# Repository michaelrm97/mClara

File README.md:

# Clara Mini

## Background

The other Project C.L.A.R.A (Christmas Light Array Running on Azure) was conceived in 2020 as an LED Christmas light display controllable from the web. See [https://github.com/michaelrm97/clara](https://github.com/michaelrm97/clara) for information about the previous project.

## Components

There are three components of this:

- PCB with an LED light array in the shape of a Christmas card
- Laser cut plywood covers glued to the back and front of the PCB. The front contains a Christmas tree graphic and the back contains a festive greeting with a QR code linking to a personal message
- Web app hosting the card message. See [README](./software/README.md)

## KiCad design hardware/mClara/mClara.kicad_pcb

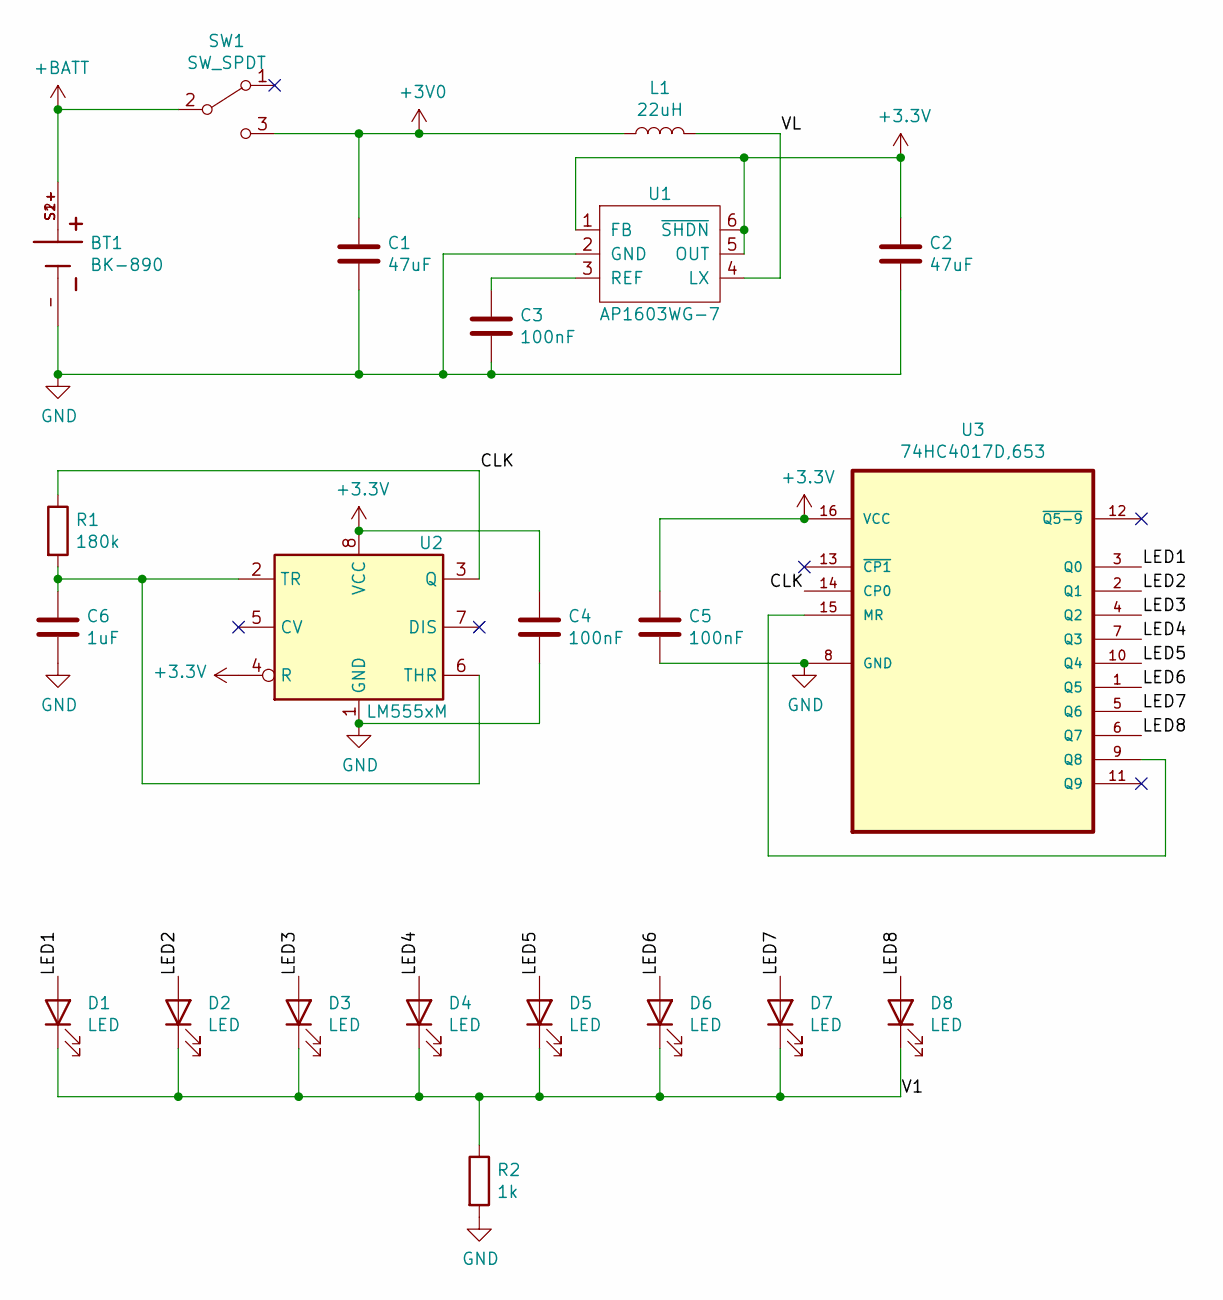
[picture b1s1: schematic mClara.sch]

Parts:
BT1: BK-890; BAT_BK-890; PARTREV E
C1, C2: 47uF; C_1206_3216Metric_Pad1.33x1.80mm_HandSolder; MPN CL31A476MQHNNWE
C3, C4, C5: 100nF; C_0603_1608Metric_Pad1.08x0.95mm_HandSolder; MPN CL10B104KB8NNWC
C6: 1uF; C_0603_1608Metric_Pad1.08x0.95mm_HandSolder; MPN CL10A105KO8NNNC
D1, D2, D3, D4, D5, D6, D7, D8: LED; LED_0603_1608Metric_Pad1.05x0.95mm_HandSolder; MPN IN-S63AT5UW
L1: 22uH; L_1812_4532Metric_Pad1.30x3.40mm_HandSolder; MPN LQH43PN220M26L
R1: 180k; R_0603_1608Metric_Pad0.98x0.95mm_HandSolder; MPN RMCF0603FT180K
R2: 1k; R_0603_1608Metric_Pad0.98x0.95mm_HandSolder; MPN RMCF0603JJ1K00
SW1: SW_SPDT; SW_PCM12SMTR; MPN PCM12SMTR
U1: AP1603WG-7; SOT-23-6_Handsoldering; MPN AP1603WG-7
U2: LM555xM; SOIC-8_3.9x4.9mm_P1.27mm; MPN TLC555IDR
U3: 74HC4017D,653; SO-16_3.9x9.9mm_P1.27mm; MPN 74HC4017D,653

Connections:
+3V0: C1.1, L1.1, SW1.3 (C)
+3V3: C2.1, C4.1, C5.1, U1.1 (FB), U1.5 (OUT), U1.6 (~SHDN), U2.4 (R), U2.8 (VCC), U3.16 (VCC)
+BATT: BT1.S1+, BT1.S2+, SW1.2 (B)
/CLK: R1.1, U2.3 (Q), U3.14 (CP0)
/LED1: D1.2 (A), U3.3 (Q0)
/LED2: D2.2 (A), U3.2 (Q1)
/LED3: D3.2 (A), U3.4 (Q2)
/LED4: D4.2 (A), U3.7 (Q3)
/LED5: D5.2 (A), U3.10 (Q4)
/LED6: D6.2 (A), U3.1 (Q5)
/LED7: D7.2 (A), U3.5 (Q6)
/LED8: D8.2 (A), U3.6 (Q7)
/V1: D1.1 (K), D2.1 (K), D3.1 (K), D4.1 (K), D5.1 (K), D6.1 (K), D7.1 (K), D8.1 (K), R2.1
/VL: L1.2, U1.4 (LX)
GND: BT1.-, C1.2, C2.2, C3.2, C4.2, C5.2, C6.2, R2.2, U1.2 (GND), U2.1 (GND), U3.8 (GND)
unnamed: C3.1, U1.3 (REF)
unnamed: C6.1, R1.2, U2.2 (TR), U2.6 (THR)
unnamed: U3.9 (Q8), U3.15 (MR)

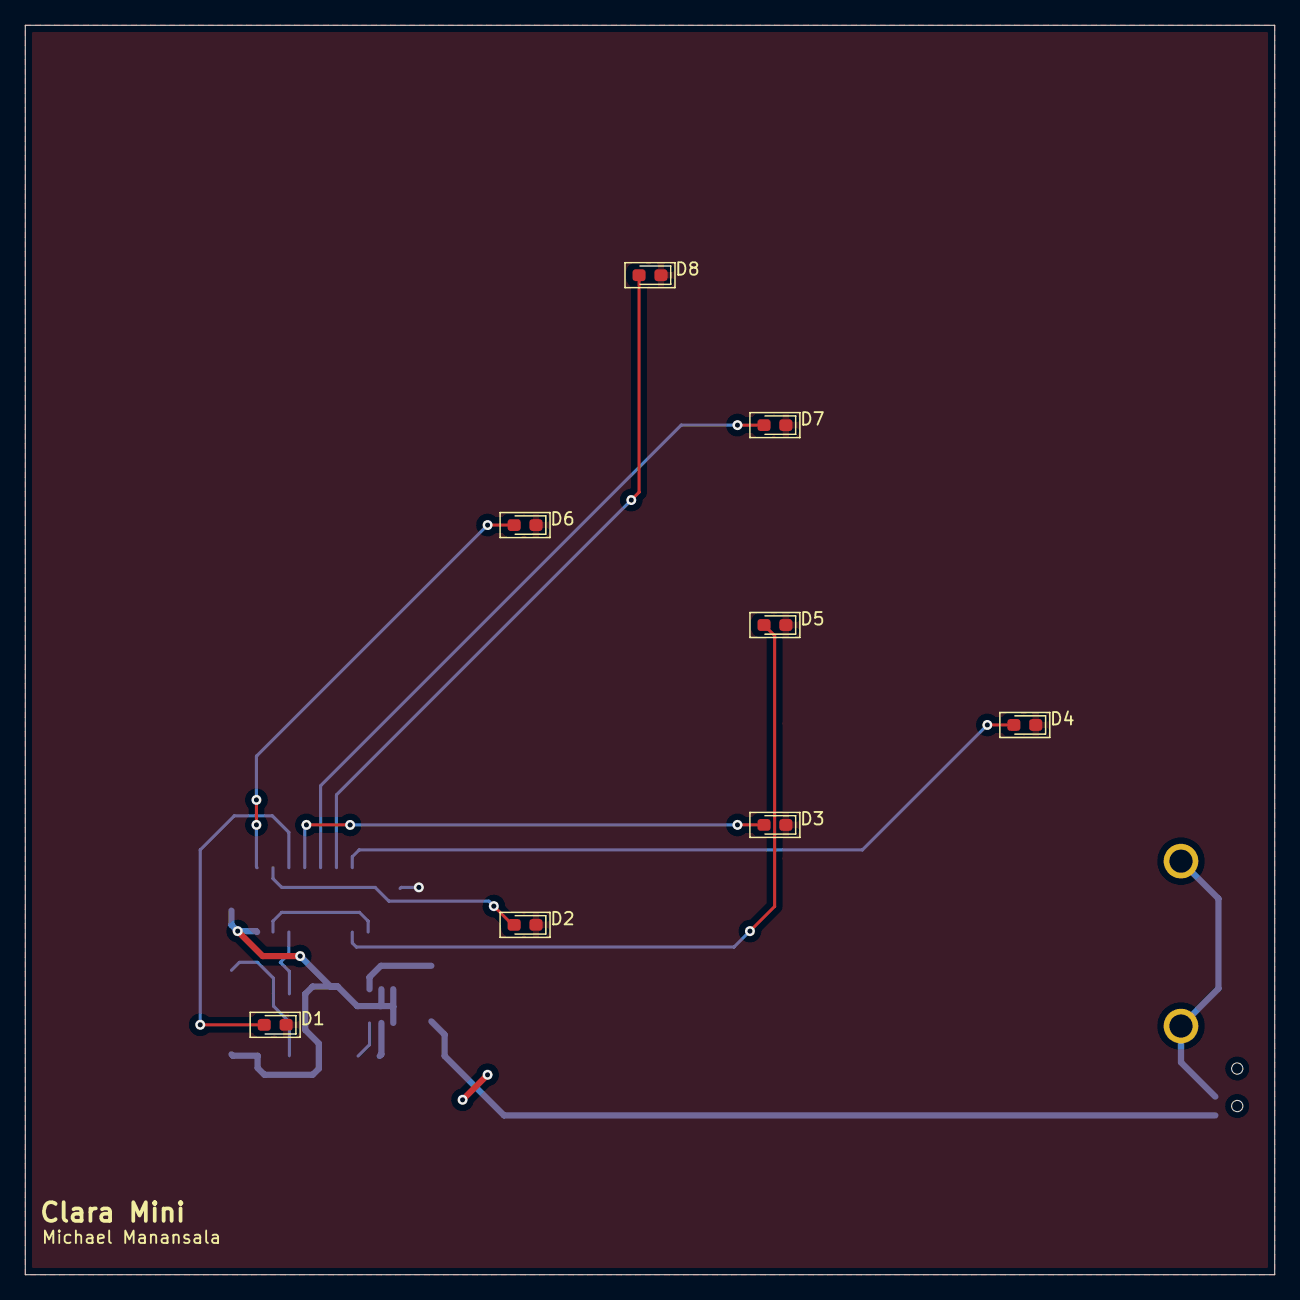
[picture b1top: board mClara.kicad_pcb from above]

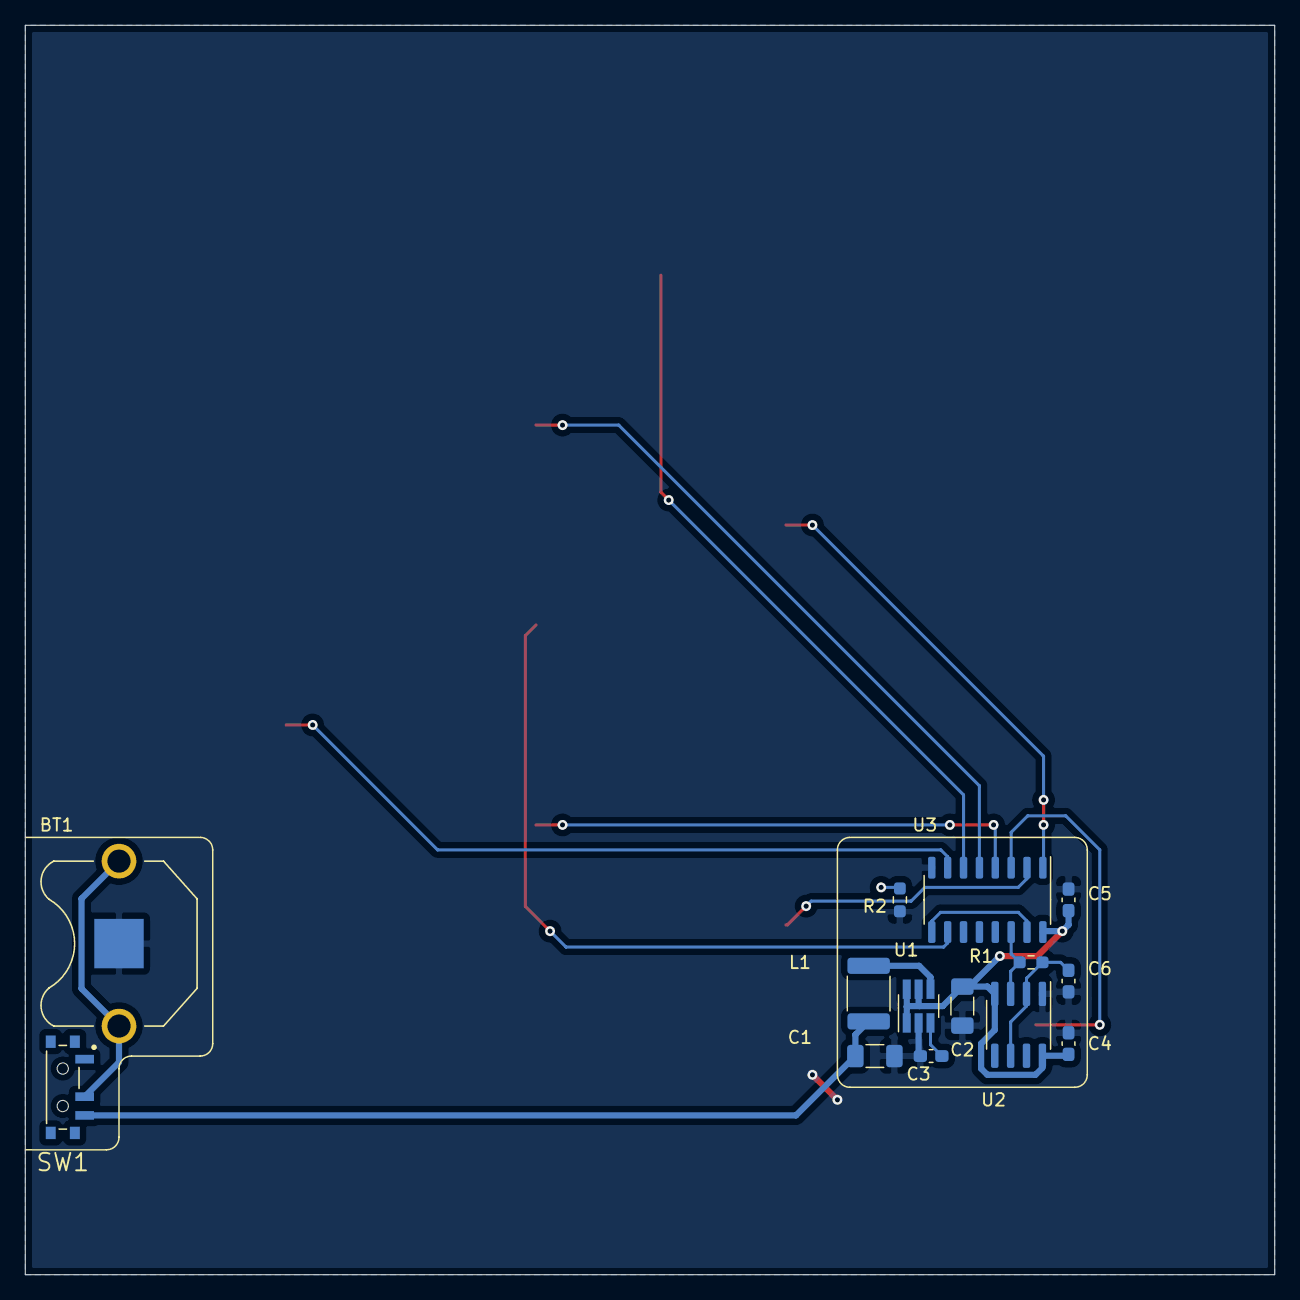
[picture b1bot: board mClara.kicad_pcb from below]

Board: 2 copper layers, 100.0 x 100.0 mm, 22 parts (14 on the bottom side), 18 nets.

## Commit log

2021-11-13 Checking in hardware and housing
2021-11-15 Created Web API
2021-11-16 Implemented basic store and PowerShell commands
2021-11-19 Implemented storage and routing
2021-11-20 Fixed routing
2021-11-20 Implemented get QR code
2021-11-21 Checked in PowerShell module
2021-11-22 Implemented rest of PowerShell cmdlets
2021-11-23 Fixed up cmdlets
2021-11-23 Updated PS binaries
2021-11-24 Implemented sync
2021-11-24 Accounted for kerf in template
2021-11-24 Added name and QR Code to temlate
2021-11-24 Added QR code generation to sync
2021-11-25 Updated routing
2021-11-26 Updated new id creation logic
2021-11-29 Modified sync behavior
2021-11-29 Fixed up templates
2021-11-29 Removed extra write objects
2021-12-06 Adjusted front and back templates
2021-12-06 Implemented navbar and home page
2021-12-07 Implemented UI
2021-12-08 Implemented reply and fixed deployment
2021-12-08 Fixed library issues
2021-12-08 Fixed sync and spacing
2021-12-12 Implemented logging for comments
2021-12-13 Added GetNames switch to Get-Logs
2021-12-18 Fixed sync issue with single folder
2021-12-31 Removed aue and added hedgehog
